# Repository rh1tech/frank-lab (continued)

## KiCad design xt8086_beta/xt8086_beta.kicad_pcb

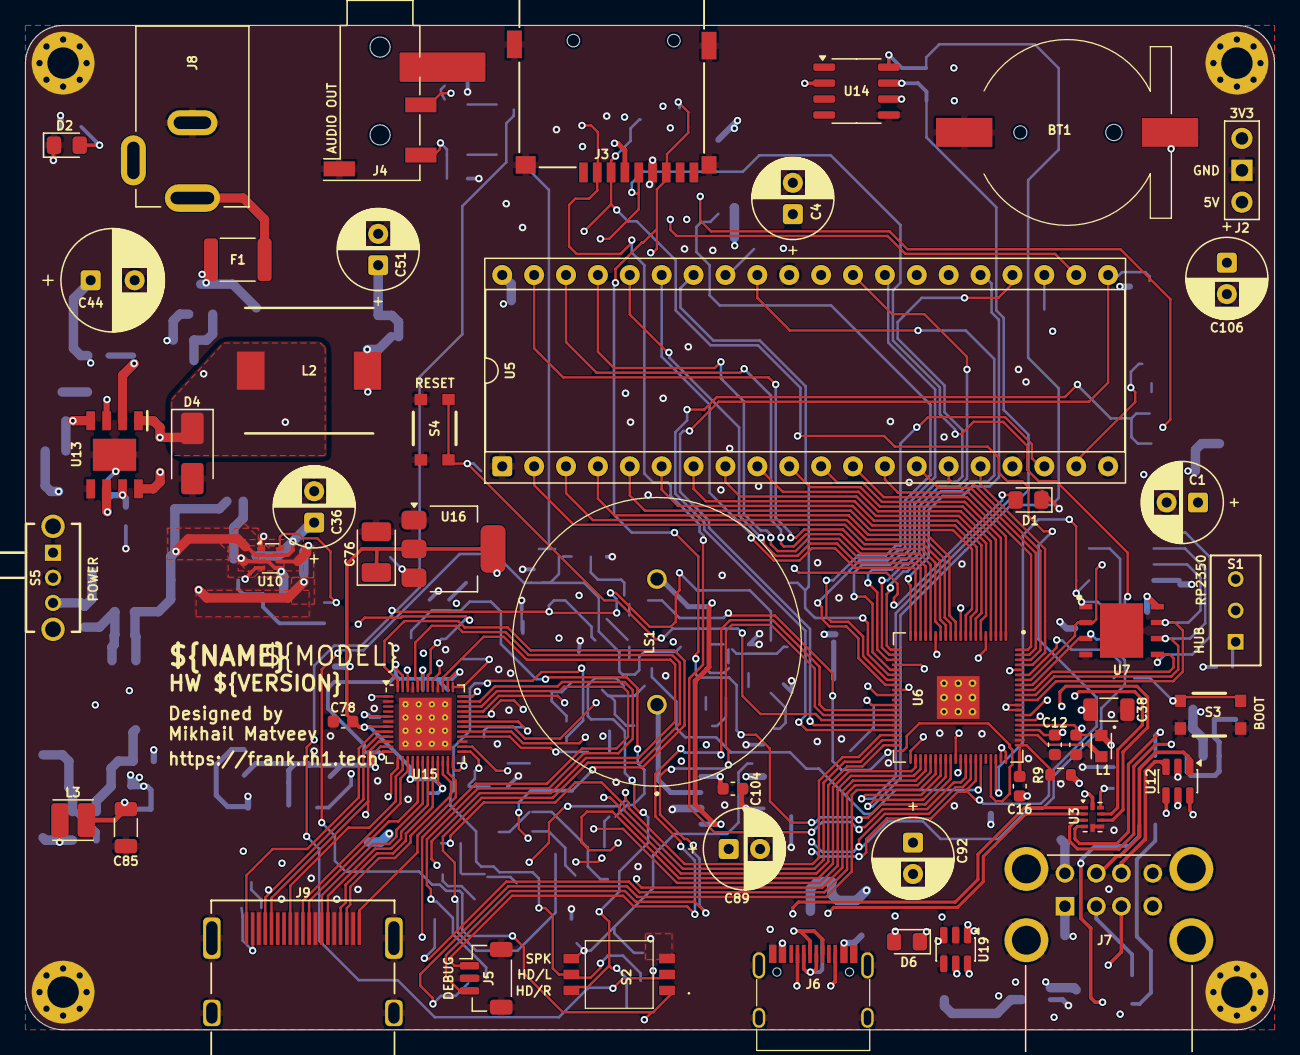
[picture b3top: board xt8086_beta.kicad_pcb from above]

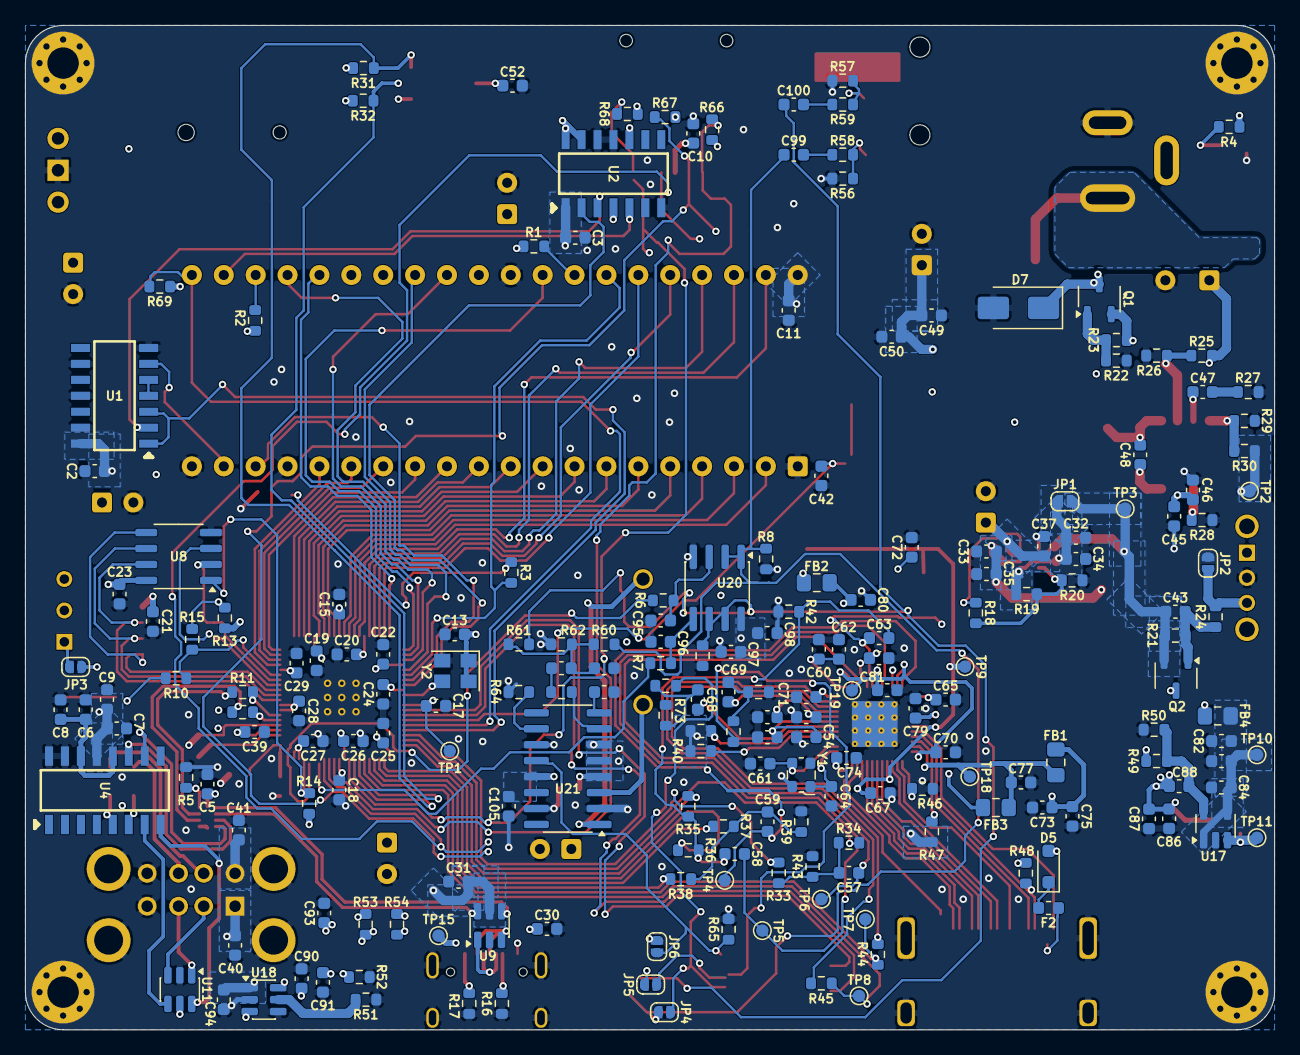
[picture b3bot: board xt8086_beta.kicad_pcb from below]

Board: 4 copper layers, 99.5 x 80.0 mm, 258 parts (203 on the bottom side), 179 nets.

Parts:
BT1: Battery_CR1220
C1, C4, C36, C89, C92, C106: 100u 25V; CP_Radial_D6.3mm_P2.50mm
C2, C3, C5, C8, C9, C10, C11, C13, C15, C18, C19, C20, C21, C22, C23, C24, C25, C26, C27, C28, C29, C30, C31, C32, C33, C37, C39, C46, C48, C49, C52, C57, C58, C59, C65, C66, C67, C70, C71, C74, C75, C84, C87, C93, C94, C97, C104: 100n 50V; C_0603_1608Metric
C6, C43, C68, C69, C78, C79, C102, C103: 1u 50V; C_0603_1608Metric
C7, C12, C14, C16, C17, C54, C56, C62: 4.7u 16V; C_0603_1608Metric
C34, C35, C40, C41, C50, C72, C73, C77, C80, C81, C82, C83, C86, C90, C91, C98, C99, C100, C105: 10u 10V; C_0603_1608Metric
C38, C85: 100u 6.3V; C_1206_3216Metric
C42, C63: 1n 50V; C_0603_1608Metric
C44: 680u 25V; CP_Radial_D8.0mm_P3.50mm
C45: 10u 25V; C_0603_1608Metric
C47: 150p 50V; C_0603_1608Metric
C51: 220u 16V; CP_Radial_D6.3mm_P2.50mm
C53, C55, C60: 220n 25V; C_0603_1608Metric
C61, C64: 15p 50V; C_0603_1608Metric
C76: 22u 16V; CP_EIA-3528-12_Kemet-T
C88: 22p 50V; C_0603_1608Metric
C95, C96: 10n 50V; C_0603_1608Metric
C101: 6.8n 50V; C_0603_1608Metric
D1, D6: Red; LED_0805_2012Metric_Pad1.15x1.40mm_HandSolder
D2: Green; LED_0805_2012Metric_Pad1.15x1.40mm_HandSolder
D4: SS34; D_SMA
D5: 1N5819WS; D_SOD-323
D7: SMAJ15A; D_SMA
F1: 1.5A 24V; Fuse_1812_4532Metric
F2: 0.2A 9V; Fuse_0603_1608Metric
FB1, FB2, FB3: 220Ω@100MHz; L_0805_2012Metric
FB4: 330Ω@100MHz 2A; L_0805_2012Metric
H1, H2, H3, H4: Hole 2.5mm; MountingHole_2.5mm_Pad_Via
J2: PWR; PinHeader_1x03_P2.54mm_Vertical
J3: 693072010801; MicroSD_SMD_Long
J4: PJ-320D; AudioJack_3.5mm_PJ320D_AudioOut
J5: Debug; JST_SH_1x03_P1.00mm_Vertical
J6: USB4215-03-A; USB_C_Receptacle
J7: SS-52100-004; USB_A_Stacked
J8: DC-005-5A-2.0; BarrelJack_DC-005
J9: DC3RX19JA2; HDMI_Female
JP1: Power Debug; SolderJumper-2_P1.0mm_Open_RoundedPad0.7x1.0mm
JP2: Force On; SolderJumper-2_P1.0mm_Open_RoundedPad0.7x1.0mm
JP3: USB Test; SolderJumper-2_P1.0mm_Open_RoundedPad0.7x1.0mm
JP4: Audio L; SolderJumper-2_P1.0mm_Open_RoundedPad0.7x1.0mm
JP5: Audio R; SolderJumper-2_P1.0mm_Open_RoundedPad0.7x1.0mm
JP6: Speaker; SolderJumper-2_P1.0mm_Open_RoundedPad0.7x1.0mm
L1: 3.3µH; L_LQH2MCN100K02L
L2: 22µH; Inductor_CDRH104RNP
L3: 2.2µH; L_Cenker_CKCS3015
LS1: 2308 1W 8Ω; CVS-2308
Q1, Q2: AO3401A; SOT-23-3L_AOS
R1, R2, R3, R4, R6, R7, R10, R46, R54: 1kΩ; R_0603_1608Metric
R5, R13, R14, R24, R63, R64, R65, R66, R67, R68, R69, R73, R75: 10kΩ; R_0603_1608Metric
R8, R55: 2.2kΩ; R_0603_1608Metric
R9: 33Ω; R_0603_1608Metric
R11, R12: 27Ω; R_0603_1608Metric
R15, R72, R74: 0Ω; R_0603_1608Metric
R16, R17: 5.1kΩ; R_0603_1608Metric
R18: 1MΩ; R_0603_1608Metric
R19, R25: 300kΩ; R_0603_1608Metric
R20, R21, R22, R26, R27, R28, R49, R51, R52, R53: 100kΩ; R_0603_1608Metric
R23, R30: 43kΩ; R_0603_1608Metric
R29: 8.2kΩ; R_0603_1608Metric
R31, R32, R40, R41: 4.7kΩ; R_0603_1608Metric
R33, R35, R37: 806Ω; R_0603_1608Metric
R34, R36, R38, R58, R59: 402Ω; R_0603_1608Metric
R39, R42, R43: 75Ω; R_0603_1608Metric
R44, R45: 100Ω; R_0603_1608Metric
R47, R48, R62: 2kΩ; R_0603_1608Metric
R50, R60, R61: 22kΩ; R_0603_1608Metric
R56, R57: 20kΩ; R_0603_1608Metric
S1: SS12D00; Switch_Slide_SS12D00
S2: DS05-127-2-03BK-SMT-TR; SW_DIP_DS05-127-2-03BK-SMT
S3: Boot; Button_SMD_3x4x2mm
S4: Reset; Button_SMD_3x4x2mm
S5: SK12D07VG3NS; Switch_Slide_SK12D07VG3NS
TP1: +1V1; TestPoint_Pad_D1.0mm
TP2: +5V_DC; TestPoint_Pad_D1.0mm
TP3: +5V_SEL; TestPoint_Pad_D1.0mm
TP4: R; TestPoint_Pad_D1.0mm
TP5: G; TestPoint_Pad_D1.0mm
TP6: B; TestPoint_Pad_D1.0mm
TP7: HS; TestPoint_Pad_D1.0mm
TP8: VS; TestPoint_Pad_D1.0mm
TP9: AMS_1V8; TestPoint_Pad_D1.0mm
TP10: +5V_BUCK; TestPoint_Pad_D1.0mm
TP11: LX; TestPoint_Pad_D1.0mm
TP15: VBUS_USB; TestPoint_Pad_D1.0mm
TP18: AMS_3V3; TestPoint_Pad_D1.0mm
TP19: AMS_3V3A; TestPoint_Pad_D1.0mm
U1: 74HCT04; SOIC127P600X175-14N
U2: SN74LS74; SOIC127P600X175-14N
U3: TS3USB221RSER; Texas_R-PUQFN-N10
U4: MW7211A; SOIC127P600X175-16N
U5: 8086_Min_Mode; DIP-40_W15.24mm_Socket
U6: RP2350B; RP2350-QFN-80_10x10_P0.4mm
U7: W25Q128JVPIQ; SON127P600X500X80-9N-D
U8: ESP-PSRAM64H; SO-8
U9, U11, U12: USBLC6-2SC6; SOT-23-6
U10: TPS2116DRL; SOT-583-8
U13: MP1584EN-LF-Z; SOIC-9_P1.27mm
U14: DS3231MZ; SO-8
U15: MS9288A; QFN-48_6x6mm_P0.4mm
U16: AMS1117-1.8; SOT-223-3_TabPin2
U17: SY8089AAAC; SOT-23-5
U18, U19: CH217K; SOT-23-6
U20: LM358; SOIC-8_3.9x4.9mm_P1.27mm
U21: PAM8403D; SOP-16_P1.27mm
Y1: 24.576MHz; Crystal_SMD_2520-4Pin
Y2: 12MHz; Oscillator_SMD_3225_4Pin

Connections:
+1V1: C14.1, C15.1, C17.1, C18.1, L1.1, TP1.1, U6.10 (DVDD), U6.32 (DVDD), U6.51 (DVDD), U6.65 (VREG_FB)
+3V3: C5.2, C10.2, C12.1, C13.1, C19.1, C20.1, C21.1, C22.1, C23.1, C24.1, C25.1, C26.1, C27.1, C28.1, C29.1, C38.1, C39.1, C52.1, C73.1, C75.1, C85.1, C86.1, C87.1, C88.1, FB1.1, J2.3, J3.4 (VDD), JP3.1, L3.2, R4.2, R9.1, R13.2, R14.2, R31.2, R32.2, R40.2, R41.2, R49.1, R66.1, R67.1, R68.1, R69.1, S1.2, U3.10 (VCC), U6.5 (IOVDD), U6.15 (IOVDD), U6.24 (IOVDD), U6.29 (IOVDD), U6.41 (IOVDD), U6.50 (IOVDD), U6.59 (ADC_AVDD), U6.60 (IOVDD), U6.64 (VREG_VIN), U6.68 (USB_OTP_VDD), U6.69 (QSPI_IOVDD), U6.76 (IOVDD), U7.8 (VCC), U8.8 (VCC), U14.2 (VCC), Y2.1 (EN), Y2.4 (Vdd)
+5V_DC: C32.2, C34.2, C49.2, C50.1, C51.1, JP1.1, L2.2, R19.2, R30.1, TP2.1, U10.3 (VIN1), U10.5 (MODE)
+5V_SEL: C31.2, C36.1, C37.1, C43.1, JP1.2, Q2.2 (S), R21.1, TP3.1, U9.5 (VBUS), U10.2 (VOUT), U10.7 (VOUT)
/A16/GP16: U5.38 (A16/S3), U6.16 (GPIO16)
/A17/GP17: U5.37 (A17/S4), U6.17 (GPIO17)
/A18/GP18: U5.36 (A18/S5), U6.18 (GPIO18)
/A19/GP19: U5.35 (A19/S6), U6.19 (GPIO19)
/AD0/GP0: U5.16 (AD0), U6.77 (GPIO0)
/AD1/GP1: U5.15 (AD1), U6.78 (GPIO1)
/AD2/GP2: U5.14 (AD2), U6.79 (GPIO2)
/AD3/GP3: U5.13 (AD3), U6.80 (GPIO3)
/AD4/GP4: U5.12 (AD4), U6.1 (GPIO4)
/AD5/GP5: U5.11 (AD5), U6.2 (GPIO5)
/AD6/GP6: U5.10 (AD6), U6.3 (GPIO6)
/AD7/GP7: U5.9 (AD7), U6.4 (GPIO7)
/AD8/GP8: U5.8 (AD8), U6.6 (GPIO8)
/AD9/GP9: U5.7 (AD9), U6.7 (GPIO9)
/AD10/GP10: U5.6 (AD10), U6.8 (GPIO10)
/AD11/GP11: U5.5 (AD11), U6.9 (GPIO11)
/AD12/GP12: U5.4 (AD12), U6.11 (GPIO12)
/AD13/GP13: U5.3 (AD13), U6.12 (GPIO13)
/AD14/GP14: U5.2 (AD14), U6.13 (GPIO14)
/AD15/GP15: U5.39 (AD15), U6.14 (GPIO15)
/ALE/GP20: U5.25 (ALE), U6.20 (GPIO20)
/BHE/GP25: R3.2, U5.34 (~BHE/S7), U6.26 (GPIO25)
/CLK_5V: U1.6 (3Y), U5.19 (CLK)
/CLK/GP29: U1.1 (1A), U1.3 (2A), U6.37 (GPIO29)
/GP27: U2.2 (D1), U6.28 (GPIO27)
/HDMI_L: JP4.2, R72.1, S2.2
/HDMI_R: JP5.2, R74.1, S2.4
/INTA/GP23: U5.24 (~INTA), U6.23 (GPIO23)
/INTR/GP26: U5.18 (INTR), U6.27 (GPIO26)
/MIO/GP24: U5.28 (M/~IO), U6.25 (GPIO24)
/MN/MX: R1.2, U5.33 (MN/~MX)
/Micro SD/CDDAT3: J3.2 (DAT3/CD), R66.2, U6.52 (GPIO41_ADC1)
/Micro SD/CLK: J3.5 (CLK), U6.53 (GPIO42_ADC2)
/Micro SD/CMD: J3.3 (CMD), R67.2, U6.54 (GPIO43_ADC3)
/Micro SD/DAT0: J3.7 (DAT0), R68.2, U6.49 (GPIO40_ADC0)
/PWM_L: R6.1, U6.57 (GPIO46_ADC6)
/PWM_R: R7.1, U6.55 (GPIO44_ADC4)
/RD/GP21: U5.32 (~RD), U6.21 (GPIO21)
/READY: U2.5 (Q1), U5.22 (READY)
/RESET/GP28: R69.2, U5.21 (RESET), U6.36 (GPIO28)
/RP2350B/DM: R12.1, U3.7 (D-)
/RP2350B/DP: R11.1, U3.8 (D+)
/RP2350B/GP30: R33.1, U6.38 (GPIO30)
/RP2350B/GP31: R34.1, U6.39 (GPIO31)
/RP2350B/GP32: R35.1, U6.40 (GPIO32)
/RP2350B/GP33: R36.1, U6.42 (GPIO33)
/RP2350B/GP34: R37.1, U6.43 (GPIO34)
/RP2350B/GP35: R38.1, U6.44 (GPIO35)
/RP2350B/GP36: R44.1, TP7.1, U6.45 (GPIO36)
/RP2350B/GP37: R45.1, TP8.1, U6.46 (GPIO37)
/RP2350B/GP38: R32.1, U6.47 (GPIO38), U14.7 (SDA)
/RP2350B/GP39: R31.1, U6.48 (GPIO39), U14.8 (SCL)
/RP2350B/GP47: R14.1, U6.58 (GPIO47_ADC7), U8.1 (~CE)
/RP2350B/QSPI_SCLK: U6.71 (QSPI_SCLK), U7.6 (CLK), U8.6 (SCLK)
/RP2350B/QSPI_SD0: U6.72 (QSPI_SD0), U7.5 (DI_(IO0)), U8.5 (SI/SIO)
/RP2350B/QSPI_SD1: U6.74 (QSPI_SD1), U7.2 (DO_(IO1)), U8.2 (SO/SIO)
/RP2350B/QSPI_SD2: U6.73 (QSPI_SD2), U7.3 (~WP_(IO2)), U8.3 (SIO2)
/RP2350B/QSPI_SD3: U6.70 (QSPI_SD3), U7.7 (~HOLD_OR_/RESET_(IO3)), U8.7 (SIO3)
/RP2350B/QSPI_SS: R10.1, R15.1, U6.75 (QSPI_SS)
/RP2350B/Reset/RESET: C42.2, S4.2, S4.4, U6.35 (RUN)
/RP2350B/SWCLK: J5.3, U6.33 (SWCLK)
/RP2350B/SWD: J5.1, U6.34 (SWD)
/RP2350B/VREG_AVDD: C16.1, R9.2, U6.61 (VREG_AVDD)
/RP2350B/VREG_LX: L1.2, U6.63 (VREG_LX)
/RP2350B/XIN: U6.30 (XIN), Y2.3 (OUT)
/RP2350B/~USB_BOOT: R10.2, S3.2, S3.4
/Sound/AUDIO_L: C99.2, JP4.1, R8.1, R60.1, S2.1, U20.1, U20.2
/Sound/AUDIO_R: C100.2, JP5.1, R55.1, R61.1, S2.3, U20.6, U20.7
/Sound/SPK_EN: JP6.2, R65.1, S2.6, U21.12
/Sound/Speaker/SPK_N: LS1.1, U21.3
/Sound/Speaker/SPK_P: LS1.2, U21.1
/TEST: R2.2, U5.23 (~TEST)
/USB, Power/3V3 Buck/+5V_BUCK: C82.1, C83.1, C84.1, FB4.2, TP10.1, U17.1 (EN), U17.4 (IN)
/USB, Power/3V3 Buck/FB: C88.2, R49.2, R50.1, U17.5 (FB)
/USB, Power/Power/VIN: C44.1, C45.1, C46.1, Q1.2 (S), R23.2, R25.2, U13.7 (VIN)
/USB, Power/ST: R18.1, U10.8 (ST)
/USB, Power/SW: JP3.2, R5.1, S1.1, U3.9 (S)
/USB, Power/UA1M: U4.7 (DM3), U11.4 (I/O2)
/USB, Power/UA1P: U4.8 (DP3), U11.6 (I/O1)
/USB, Power/UA2M: U4.5 (DM2), U12.6 (I/O1)
/USB, Power/UA2P: U4.6 (DP2), U12.4 (I/O2)
/USB, Power/UAM: U3.4 (2D-), U4.10 (DMU)
/USB, Power/UAP: U3.3 (2D+), U4.11 (DPU)
/USB, Power/UCM: U3.2 (1D-), U9.6 (I/O1)
/USB, Power/UCP: U3.1 (1D+), U9.4 (I/O2)
/USB, Power/USB Hub/VD33: C6.1, C8.1, U4.12 (VD33), U4.14 (VD3)
/USB, Power/USB-A Port Power/USB_OC: D6.1 (K), R53.2, U18.3 (FLAG#), U19.3 (FLAG#)
/USB, Power/VBUS_P1: C40.1, C94.1, J7.1 (VBUS1), U18.1 (VOUT)
/USB, Power/VBUS_P2: C41.1, C93.1, J7.5 (VBUS2), U19.1 (VOUT)
/USB, Power/VBUS_USB: C30.1, C33.2, C35.2, J6.2 (VBUS), J6.11 (VBUS), TP15.1, U10.6 (VIN2)
/Video/ALIN: C68.1, U15.30 (ALIN)
/Video/AMS_1V8: C67.1, C76.1, C78.1, FB2.1, TP9.1, U15.7 (AVDD18), U15.16 (AVDD18), U15.21 (AVDD18), U16.2 (VO)
/Video/AMS_1V8A: C65.1, C66.1, C80.1, FB2.2, U15.1 (AVDD18_ADC), U15.41 (AVDD18_ADC), U15.46 (AVDD18_ADC)
/Video/AMS_3V3: C71.1, C72.1, C74.1, C77.1, C79.1, FB1.2, FB3.1, TP18.1, U15.5 (DVDD33), U15.11 (DVDD33), U15.24 (DVDD33), U15.36 (DVDD33), U16.3 (VI)
/Video/AMS_3V3A: C70.1, C81.1, FB3.2, TP19.1, U15.12 (AVDD33), U15.38 (AVDD33), U15.43 (AVDD33), U15.47 (AVDD33)
/Video/ARIN: C69.1, U15.33 (ARIN)
/Video/B: C57.1, TP6.1, U15.39 (B/Pb)
/Video/DCCSCL: J9.15 (SCL), R47.1, U15.10 (DCCSCL)
/Video/DDCSDA: J9.16 (SDA), R48.1, U15.9 (DDCSDA)
/Video/G: C58.1, TP5.1, U15.44 (G/Y)
/Video/HPDT: J9.19 (HOT_PLUG_DET), U15.8 (HotPlugDetect)
/Video/R: C59.1, TP4.1, U15.48 (R/Pr)
/Video/SCL: R40.1, U15.28 (SCL)
/Video/SDA: R41.1, U15.29 (SDA)
/Video/SOG_G: C58.2, C63.2, R35.2, R36.2, R42.1
/Video/TMDS_CLK+: J9.10 (CLKP), U15.15 (TMDS_CLK+)
/Video/TMDS_CLK-: J9.12 (CLKN), U15.14 (TMDS_CLK-)
/Video/TMDS_D0+: J9.7 (D0P), U15.18 (TMDS-D0+)
/Video/TMDS_D0-: J9.9 (D0N), U15.17 (TMDS_D0-)
/Video/TMDS_D1+: J9.4 (D1P), U15.20 (TMDS_D1+)
/Video/TMDS_D1-: J9.6 (D1N), U15.19 (TMDS_D1-)
/Video/TMDS_D2+: J9.1 (D2P), U15.23 (TMDS_D2+)
/Video/TMDS_D2-: J9.3 (D2N), U15.22 (TMDS_D2-)
/WR/GP22: U5.29 (~WR), U6.22 (GPIO22)
GND: BT1.2 (-), C1.2, C2.2, C3.2, C4.2, C5.1, C6.2, C7.2, C8.2, C9.2, C10.1, C11.2, C12.2, C13.2, C14.2, C15.2, C16.2, C17.2, C18.2, C19.2, C20.2, C21.2, C22.2, C23.2, C24.2, C25.2, C26.2, C27.2, C28.2, C29.2, C30.2, C31.1, C32.1, C33.1, C34.1, C35.1, C36.2, C37.2, C38.2, C39.2, C40.2, C41.2, C42.1, C44.2, C45.2, C46.2, C49.1, C50.2, C51.2, C52.2, C53.2, C54.2, C55.2, C56.2, C60.2, C61.2, C62.2, C64.2, C65.2, C66.2, C67.2, C70.2, C71.2, C72.2, C73.2, C74.2, C75.2, C76.2, C77.2, C78.2, C79.2, C80.2, C81.2, C82.2, C83.2, C84.2, C85.2, C86.2, C87.2, C89.2, C90.2, C91.2, C92.2, C93.2, C94.2, C95.2, C96.2, C97.2, C98.2, C101.2, C103.2, C104.2, C105.2, C106.2, D1.1 (K), D2.1 (K), D4.2 (A), D7.2 (A), H1.1, H2.1, H3.1, H4.1, J2.2, J3.6 (VSS), J3.SH (SHIELD), J4.S, J5.2, J6.1 (GND), J6.12 (GND), J6.13 (SHIELD), J7.4 (GND1), J7.8 (GND2), J7.SH (Shield), J8.2, J9.2 (G_D2), J9.5 (G_D1), J9.8 (G_D0), J9.11 (G_CLK), J9.17 (G_DDC/CEC), J9.20 (SHIELD1), J9.21 (SHIELD2), J9.22 (SHIELD3), J9.23 (SHIELD4), JP2.1, R5.2, R8.2, R16.1, R17.1, R20.1, R22.2, R26.2, R27.2, R28.2, R29.1, R39.2, R42.2, R43.2, R46.1, R50.2, R51.2, R52.2, R55.2, R56.2, R57.2, R62.2, R64.2, R65.2, R73.2, R75.2, S3.1, S3.3, S4.1, S4.3, S5.2, U1.7 (GND), U1.9 (4A), U1.11 (5A), U1.13 (6A), U2.7 (GND), U2.11 (CLK2), U2.12 (D2), U3.5 (GND), U3.6 (~OE), U4.15 (GND), U4.16 (GND), U5.1 (GND), U5.17 (NMI), U5.20 (GND), U5.31 (HOLD), U6.62 (VREG_PGND), U6.81 (GND), U7.4 (GND_1), U7.9 (GND_2), U8.4 (VSS), U9.2 (GND), U10.1 (GND), U11.2 (GND), U12.2 (GND), U13.5 (GND), U13.9 (EP), U14.5 (GND), U15.2 (GND), U15.6 (GND), U15.27 (GND), U15.40 (GND), U15.45 (GND), U15.49 (EP), U16.1 (GND), U17.2 (GND), U18.2 (GND), U18.4 (EN#), U19.2 (GND), U19.4 (EN#), U20.4, U21.2, U21.11, U21.15, Y1.2 (GND), Y1.4 (GND), Y2.2 (GND)
unnamed: BT1.1 (+), U14.6 (VBAT)
unnamed: C47.2, R27.1
unnamed: C57.2, R33.2, R34.2, R43.1
unnamed: C59.2, R37.2, R38.2, R39.1
unnamed: C68.2, R72.2, R73.1
unnamed: C69.2, R74.2, R75.1
unnamed: C99.1, R58.2
unnamed: C100.1, R59.2
unnamed: C101.1, C102.1, R60.2, R61.2, R62.1
unnamed: C102.2, R63.1
unnamed: D1.2 (A), R3.1
unnamed: D2.2 (A), R4.1
unnamed: C48.2, D4.1 (K), L2.1, U13.1 (SW)
unnamed: D5.1 (K), F2.2
unnamed: D6.2 (A), R54.2
unnamed: D7.1 (K), F1.2, Q1.3 (D)
unnamed: F1.1, J8.1
unnamed: J4.R, R57.1, R59.1
unnamed: J4.T, R56.1, R58.1
unnamed: J6.4 (CC1), R16.2
unnamed: J6.10 (CC2), R17.2
unnamed: J6.5 (DN2), J6.7 (DN1), U9.1 (I/O1)
unnamed: J6.6 (DP1), J6.8 (DP2), U9.3 (I/O2)
unnamed: J7.3 (D1+), U11.1 (I/O1)
unnamed: J7.2 (D1-), U11.3 (I/O2)
unnamed: J7.7 (D2+), U12.3 (I/O2)
unnamed: J7.6 (D2-), U12.1 (I/O1)
unnamed: F2.1, J9.18 (+5V)
unnamed: JP2.2, R24.2, S5.3
unnamed: Q1.1 (G), R22.1, R23.1
unnamed: C43.2, Q2.1 (G), R21.2, R24.1
unnamed: U1.2 (1Y), U2.3 (CLK1)
unnamed: U1.4 (2Y), U1.5 (3A)
unnamed: R12.2, U6.66 (USB_DM)
unnamed: R11.2, U6.67 (USB_DP)
unnamed: R13.1, R15.2, U7.1 (~CS)
unnamed: R18.2, R19.1, R20.2, U10.4 (PR1)
unnamed: C48.1, U13.8 (BST)
unnamed: C47.1, U13.3 (COMP)
unnamed: R25.1, R26.1, U13.2 (EN)
unnamed: R29.2, R30.2, U13.4 (FB)
unnamed: R28.1, U13.6 (FREQ)
unnamed: R44.2, U15.34 (HSIN)
unnamed: C60.1, C62.1, U15.37 (REFP)
unnamed: C53.1, C54.1, U15.31 (REFQ0)
unnamed: C55.1, C56.1, U15.32 (REFQ1)
unnamed: C63.1, U15.42 (SOG/Y)
unnamed: R46.2, U15.13 (SWREF1k)
unnamed: R45.2, U15.35 (VSIN)
unnamed: C64.1, U15.25 (XTI), Y1.1 (OSC)
unnamed: C61.1, U15.26 (XTO), Y1.3 (OSC)
unnamed: L3.1, TP11.1, U17.3 (LX)
unnamed: R51.1, U18.5 (ISET)
unnamed: R52.1, U19.5 (ISET)
unnamed: C95.1, R6.2, U20.3
unnamed: C96.1, R7.2, U20.5
unnamed: R63.2, U21.7
unnamed: R64.1, U21.10
unnamed: C103.1, U21.8
VBUS: C1.1, C2.1, C3.1, C4.1, C7.1, C9.1, C11.1, C89.1, C90.1, C91.1, C92.1, C97.1, C98.1, C104.1, C105.1, C106.1, D5.2 (A), FB4.1, J2.1, JP6.1, Q2.3 (D), R1.1, R2.1, R47.2, R48.2, R53.1, R54.1, S2.5, U1.14 (VCC), U2.1 (CLR1), U2.4 (PR1), U2.10 (PR2), U2.13 (CLR2), U2.14 (VCC), U4.13 (VDD5), U5.40 (VCC), U11.5 (VBUS), U12.5 (VBUS), U18.6 (VIN), U19.6 (VIN), U20.8, U21.4, U21.5, U21.6, U21.13

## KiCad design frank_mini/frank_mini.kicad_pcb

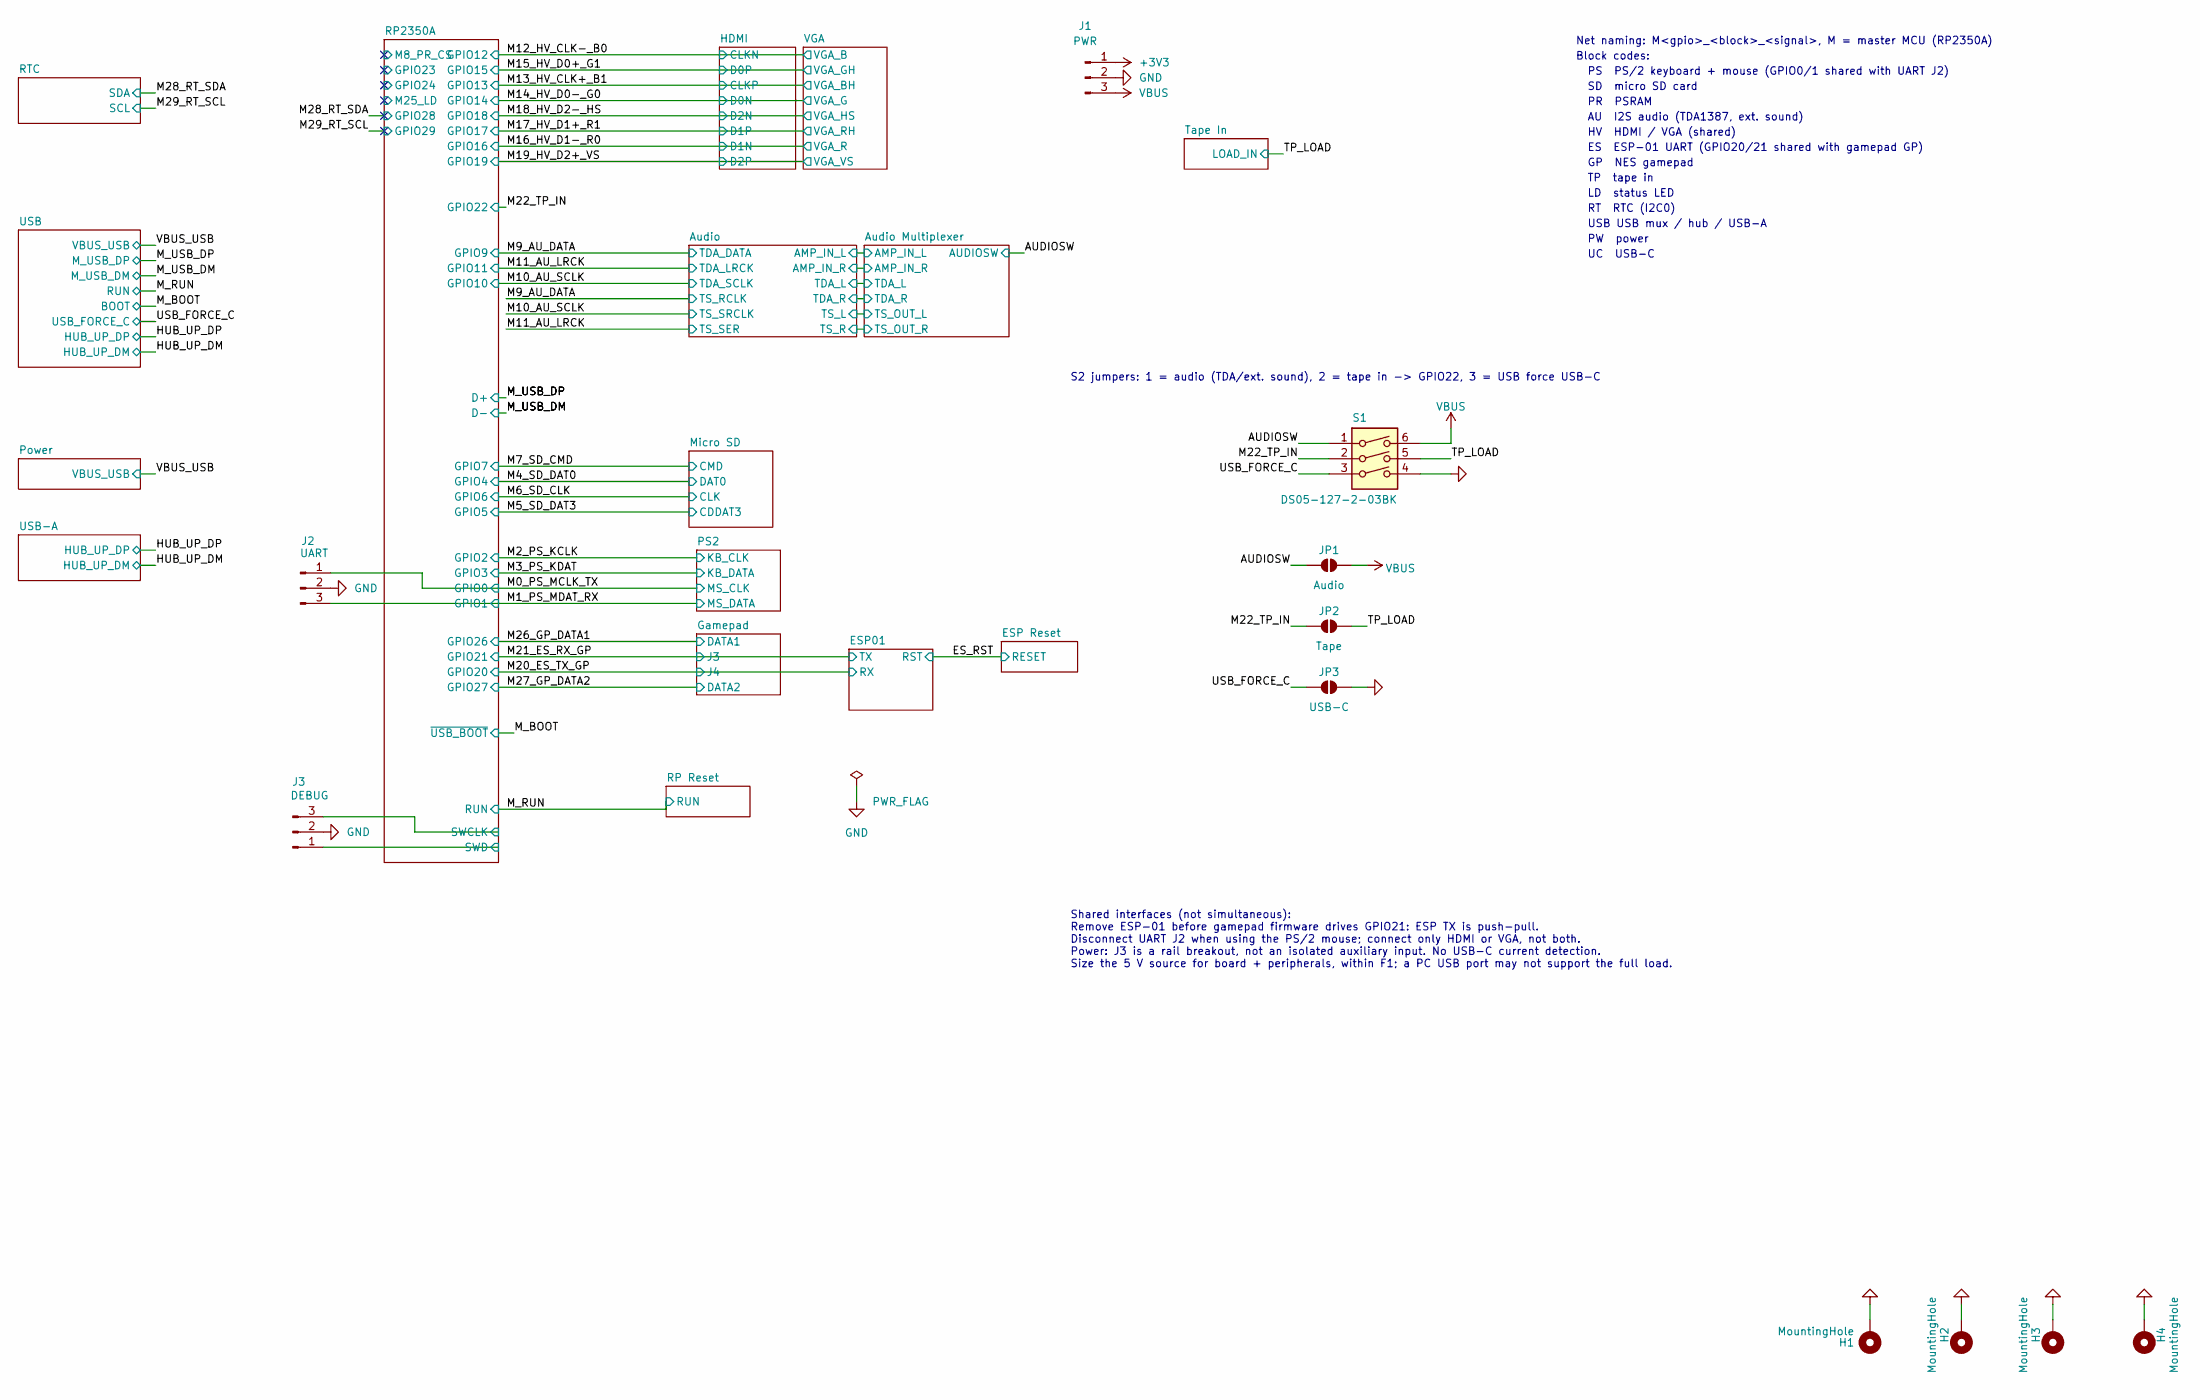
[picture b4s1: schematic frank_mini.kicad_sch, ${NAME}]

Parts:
H1, H2, H3, H4: MountingHole; MountingHole_2.5mm_Pad_Via
J1: PWR; PinHeader_1x03_P2.54mm
J2: UART; JST_SH_BM03B-SRSS-TB_1x03-1MP_P1.00mm_Vertical
J3: DEBUG; JST_SH_BM03B-SRSS-TB_1x03-1MP_P1.00mm_Vertical
JP1: Audio; SolderJumper-2_P1.3mm_Open_RoundedPad1.0x1.5mm
JP2: Tape; SolderJumper-2_P1.3mm_Open_RoundedPad1.0x1.5mm
JP3: USB-C; SolderJumper-2_P1.3mm_Open_RoundedPad1.0x1.5mm
S1: DS05-127-2-03BK; SW_DS05-127-2-03BK-SMT-TR

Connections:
+3V3: J1.1; also elsewhere on the board
/AUDIOSW: JP1.1 (A), S1.1; also elsewhere on the board
/M0_PS_MCLK_TX: J2.1; also elsewhere on the board
/M1_PS_MDAT_RX: J2.3; also elsewhere on the board
/M22_TP_IN: JP2.1 (A), S1.2; also elsewhere on the board
/RP2350A/SWCLK: J3.3; also elsewhere on the board
/RP2350A/SWD: J3.1; also elsewhere on the board
/TP_LOAD: JP2.2 (B), S1.5; also elsewhere on the board
/USB_FORCE_C: JP3.1 (A), S1.3; also elsewhere on the board
GND: H1.1 (1_1), H2.1 (1_1), H3.1 (1_1), H4.1 (1_1), J1.2, J2.2, J3.2, JP3.2 (B), S1.4; also elsewhere on the board
VBUS: J1.3, JP1.2 (B), S1.6; also elsewhere on the board

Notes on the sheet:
UC USB-C
AU I2S audio (TDA1387, ext. sound)
S2 jumpers: 1 = audio (TDA/ext. sound), 2 = tape in -> GPIO22, 3 = USB force USB-C
TP tape in
PS PS/2 keyboard + mouse (GPIO0/1 shared with UART J2)
SD micro SD card
USB USB mux / hub / USB-A
PW power
GP NES gamepad
RT RTC (I2C0)
Block codes:
LD status LED
PR PSRAM
Net naming: M<gpio>_<block>_<signal>, M = master MCU (RP2350A)
HV HDMI / VGA (shared)
ES ESP-01 UART (GPIO20/21 shared with gamepad GP)
Shared interfaces (not simultaneous): Remove ESP-01 before gamepad firmware drives GPIO21: ESP TX is push-pull. Disconnect UART J2 when using the PS/2 mouse; connect only HDMI or VGA, not both. Power: J3 is a rail breakout, not an isolated auxiliary input. No USB-C current detection. Size the 5 V s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

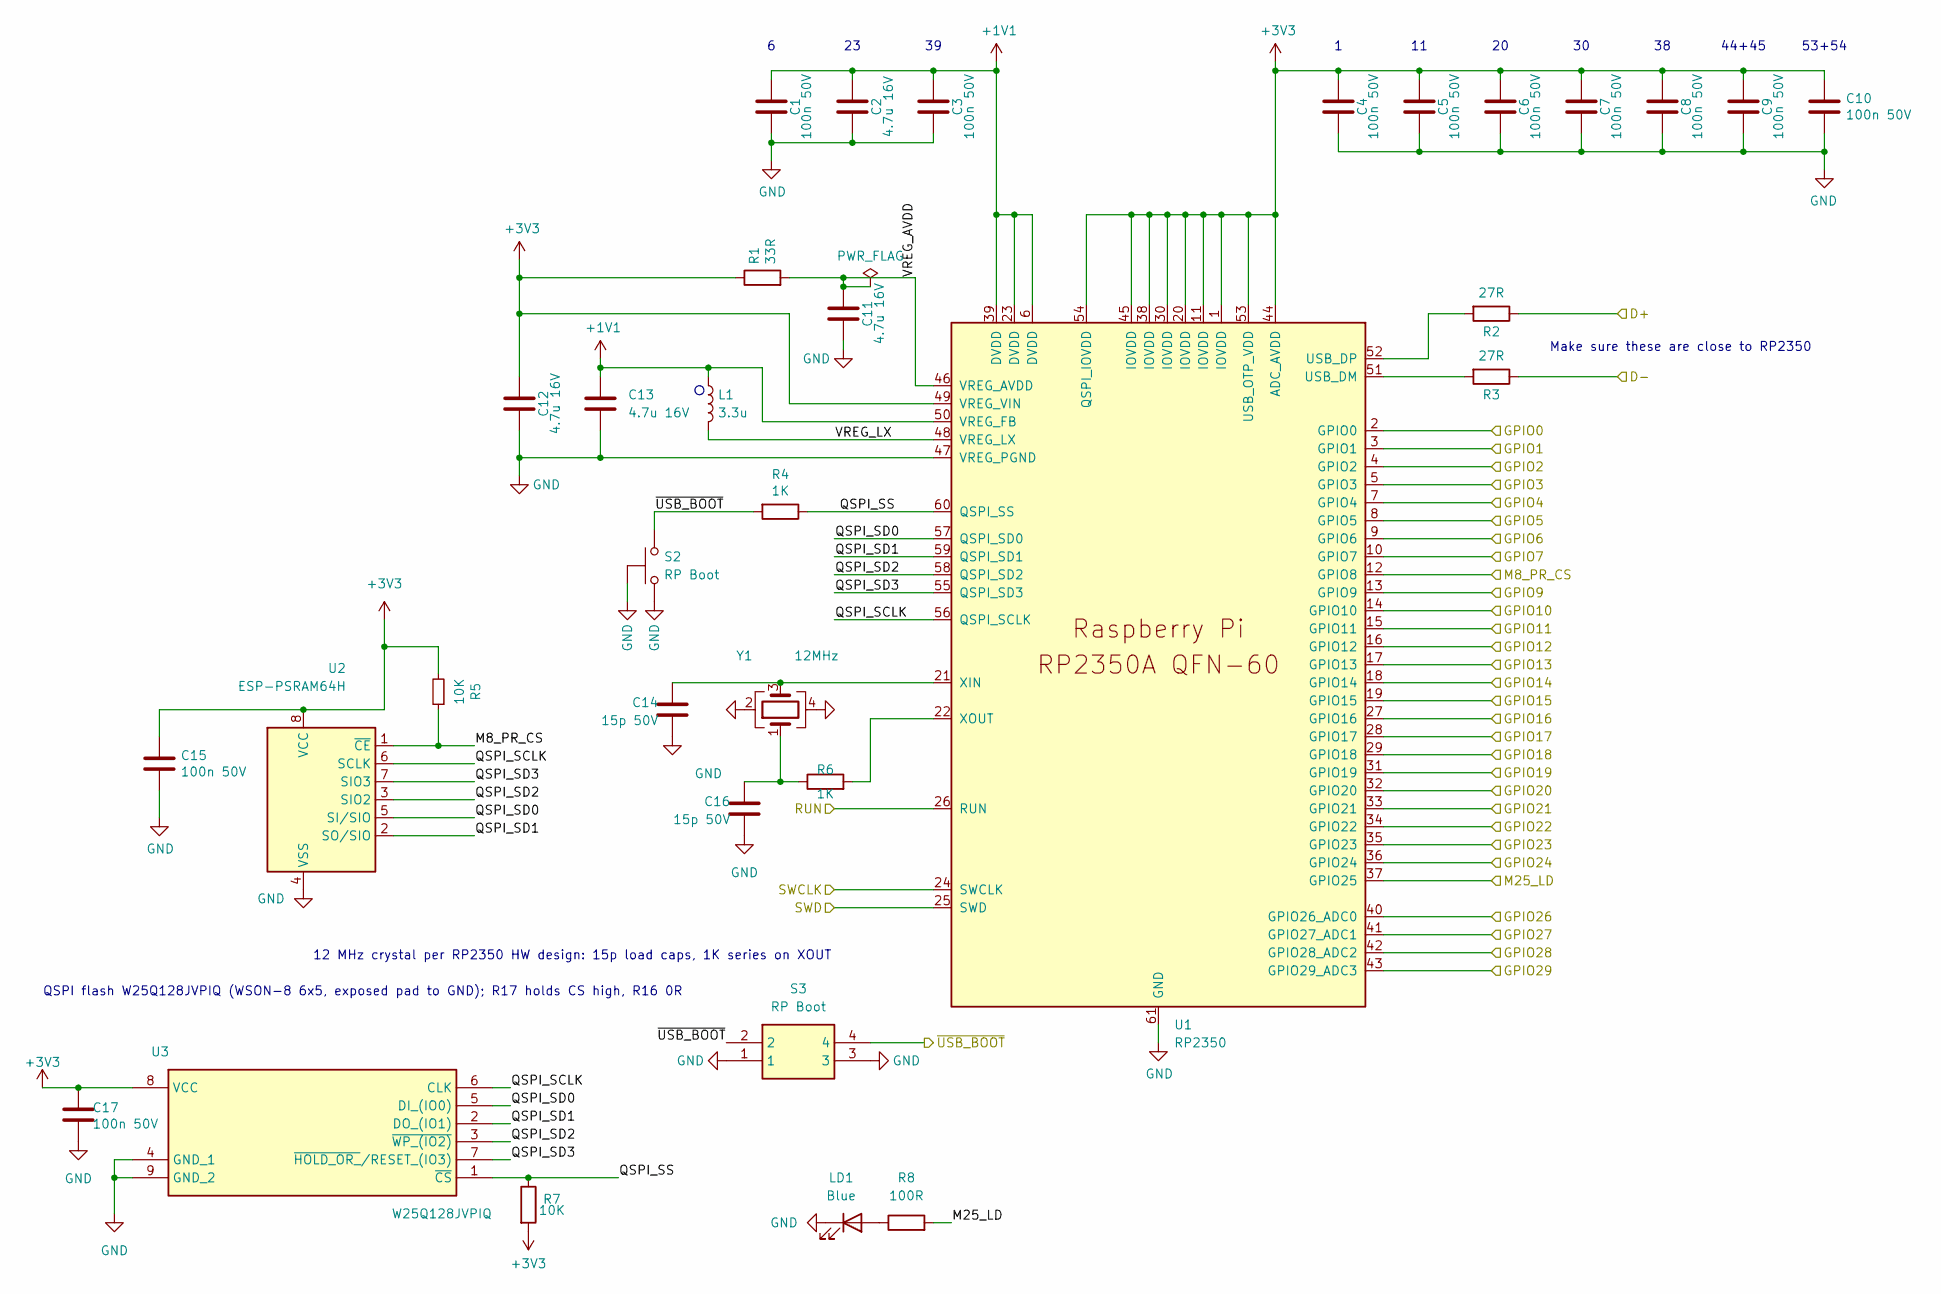
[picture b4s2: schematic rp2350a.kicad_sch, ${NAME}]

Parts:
C1, C3, C4, C5, C6, C7, C8, C9, C10, C15, C17: 100n 50V; C_0603_1608Metric
C2, C11, C12, C13: 4.7u 16V; C_0603_1608Metric
C14, C16: 15p 50V; C_0603_1608Metric
L1: 3.3u; L_pol_2016
LD1: Blue; LED_0603_1608Metric
R1: 33R; R_0603_1608Metric
R2, R3: 27R; R_0603_1608Metric
R4, R6: 1K; R_0603_1608Metric
R5, R7: 10K; R_0603_1608Metric
R8: 100R; R_0603_1608Metric
S2: RP Boot; TS-1234VW
S3: RP Boot; KMR_2; Mouser Part Number 611-KMR221G-LFS
U1: RP2350; QFN-60_RP2350A
U2: ESP-PSRAM64H; SO-8
U3: W25Q128JVPIQ; WSON-8-1EP_6x5mm_P1.27mm_EP3.45x4.35mm
Y1: 12MHz; Crystal_SMD_3225-4Pin_3.2x2.5mm

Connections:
+1V1: C1.1, C2.1, C3.1, C13.1, L1.1, U1.6 (DVDD), U1.23 (DVDD), U1.39 (DVDD), U1.50 (VREG_FB); also elsewhere on the board
+3V3: C4.1, C5.1, C6.1, C7.1, C8.1, C9.1, C10.1, C12.1, C15.1, C17.1, R1.1, R5.2, R7.2, U1.1 (IOVDD), U1.11 (IOVDD), U1.20 (IOVDD), U1.30 (IOVDD), U1.38 (IOVDD), U1.44 (ADC_AVDD), U1.45 (IOVDD), U1.49 (VREG_VIN), U1.53 (USB_OTP_VDD), U1.54 (QSPI_IOVDD), U2.8 (VCC), U3.8 (VCC); also elsewhere on the board
/M0_PS_MCLK_TX: U1.2 (GPIO0); also elsewhere on the board
/M1_PS_MDAT_RX: U1.3 (GPIO1); also elsewhere on the board
/M2_PS_KCLK: U1.4 (GPIO2); also elsewhere on the board
/M3_PS_KDAT: U1.5 (GPIO3); also elsewhere on the board
/M4_SD_DAT0: U1.7 (GPIO4); also elsewhere on the board
/M5_SD_DAT3: U1.8 (GPIO5); also elsewhere on the board
/M6_SD_CLK: U1.9 (GPIO6); also elsewhere on the board
/M7_SD_CMD: U1.10 (GPIO7); also elsewhere on the board
/M9_AU_DATA: U1.13 (GPIO9); also elsewhere on the board
/M10_AU_SCLK: U1.14 (GPIO10); also elsewhere on the board
/M11_AU_LRCK: U1.15 (GPIO11); also elsewhere on the board
/M12_HV_CLK-_B0: U1.16 (GPIO12); also elsewhere on the board
/M13_HV_CLK+_B1: U1.17 (GPIO13); also elsewhere on the board
/M14_HV_D0-_G0: U1.18 (GPIO14); also elsewhere on the board
/M15_HV_D0+_G1: U1.19 (GPIO15); also elsewhere on the board
/M16_HV_D1-_R0: U1.27 (GPIO16); also elsewhere on the board
/M17_HV_D1+_R1: U1.28 (GPIO17); also elsewhere on the board
/M18_HV_D2-_HS: U1.29 (GPIO18); also elsewhere on the board
/M19_HV_D2+_VS: U1.31 (GPIO19); also elsewhere on the board
/M20_ES_TX_GP: U1.32 (GPIO20); also elsewhere on the board
/M21_ES_RX_GP: U1.33 (GPIO21); also elsewhere on the board
/M22_TP_IN: U1.34 (GPIO22); also elsewhere on the board
/M26_GP_DATA1: U1.40 (GPIO26_ADC0); also elsewhere on the board
/M27_GP_DATA2: U1.41 (GPIO27_ADC1); also elsewhere on the board
/M28_RT_SDA: U1.42 (GPIO28_ADC2); also elsewhere on the board
/M29_RT_SCL: U1.43 (GPIO29_ADC3); also elsewhere on the board
/M_BOOT: R4.2, S2.2, S3.2, S3.4; also elsewhere on the board
/M_RUN: U1.26 (RUN); also elsewhere on the board
/M_USB_DM: R3.1; also elsewhere on the board
/M_USB_DP: R2.1; also elsewhere on the board
/RP2350A/GPIO23: U1.35 (GPIO23)
/RP2350A/GPIO24: U1.36 (GPIO24)
/RP2350A/M8_PR_CS: R5.1, U1.12 (GPIO8), U2.1 (~CE)
/RP2350A/M25_LD: R8.2, U1.37 (GPIO25)
/RP2350A/QSPI_SCLK: U1.56 (QSPI_SCLK), U2.6 (SCLK), U3.6 (CLK)
/RP2350A/QSPI_SD0: U1.57 (QSPI_SD0), U2.5 (SI/SIO), U3.5 (DI_(IO0))
/RP2350A/QSPI_SD1: U1.59 (QSPI_SD1), U2.2 (SO/SIO), U3.2 (DO_(IO1))
/RP2350A/QSPI_SD2: U1.58 (QSPI_SD2), U2.3 (SIO2), U3.3 (~WP_(IO2))
/RP2350A/QSPI_SD3: U1.55 (QSPI_SD3), U2.7 (SIO3), U3.7 (~HOLD_OR_/RESET_(IO3))
/RP2350A/QSPI_SS: R4.1, R7.1, U1.60 (QSPI_SS), U3.1 (~CS)
/RP2350A/SWCLK: U1.24 (SWCLK); also elsewhere on the board
/RP2350A/SWD: U1.25 (SWD); also elsewhere on the board
/RP2350A/VREG_AVDD: C11.1, R1.2, U1.46 (VREG_AVDD)
/RP2350A/VREG_LX: L1.2, U1.48 (VREG_LX)
GND: C1.2, C2.2, C3.2, C4.2, C5.2, C6.2, C7.2, C8.2, C9.2, C10.2, C11.2, C12.2, C13.2, C14.2, C15.2, C16.2, C17.2, LD1.1 (K), S2.1, S2.3 (GND), S3.1, S3.3, U1.47 (VREG_PGND), U1.61 (GND), U2.4 (VSS), U3.4 (GND_1), U3.9 (GND_2), Y1.2, Y1.4; also elsewhere on the board
unnamed: C16.1, R6.1, Y1.1
unnamed: LD1.2 (A), R8.1
unnamed: R3.2, U1.51 (USB_DM)
unnamed: R2.2, U1.52 (USB_DP)
unnamed: C14.1, U1.21 (XIN), Y1.3
unnamed: R6.2, U1.22 (XOUT)

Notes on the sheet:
12 MHz crystal per RP2350 HW design: 15p load caps, 1K series on XOUT
53+54
44+45
Make sure these are close to RP2350
QSPI flash W25Q128JVPIQ (WSON-8 6x5, exposed pad to GND); R17 holds CS high, R16 0R

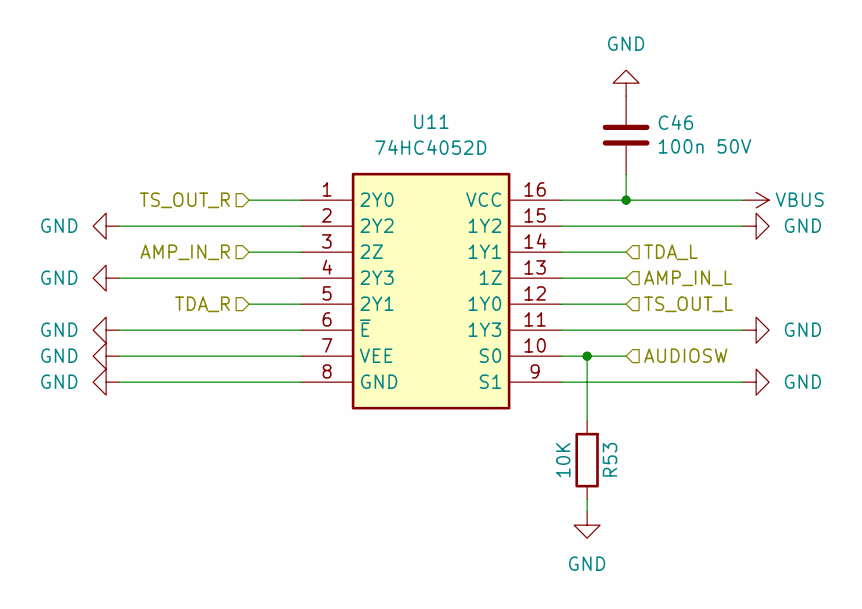
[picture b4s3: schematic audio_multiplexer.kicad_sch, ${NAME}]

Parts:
C46: 100n 50V; C_0603_1608Metric
R53: 10K; R_0603_1608Metric
U11: 74HC4052D; SOP-16_P1.27mm; Mouser Part Number 771-74HC4052D-T

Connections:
/AUDIOSW: R53.2, U11.10 (S0); also elsewhere on the board
/Audio Multiplexer/AMP_IN_L: U11.13 (1Z); also elsewhere on the board
/Audio Multiplexer/AMP_IN_R: U11.3 (2Z); also elsewhere on the board
/Audio Multiplexer/TDA_L: U11.14 (1Y1); also elsewhere on the board
/Audio Multiplexer/TDA_R: U11.5 (2Y1); also elsewhere on the board
/Audio Multiplexer/TS_OUT_L: U11.12 (1Y0); also elsewhere on the board
/Audio Multiplexer/TS_OUT_R: U11.1 (2Y0); also elsewhere on the board
GND: C46.1, R53.1, U11.2 (2Y2), U11.4 (2Y3), U11.6 (~E), U11.7 (VEE), U11.8 (GND), U11.9 (S1), U11.11 (1Y3), U11.15 (1Y2); also elsewhere on the board
VBUS: C46.2, U11.16 (VCC); also elsewhere on the board

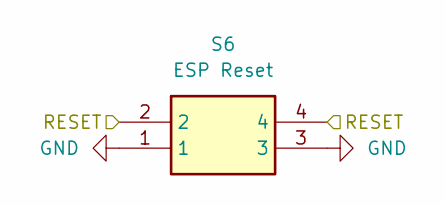
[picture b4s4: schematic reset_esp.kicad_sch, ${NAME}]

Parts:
S6: ESP Reset; KMR_2; Mouser Part Number 611-KMR221G-LFS

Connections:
/ES_RST: S6.2, S6.4; also elsewhere on the board
GND: S6.1, S6.3; also elsewhere on the board

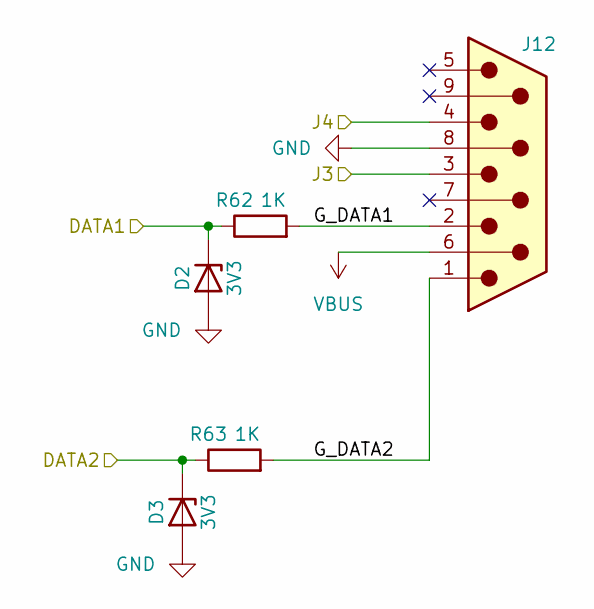
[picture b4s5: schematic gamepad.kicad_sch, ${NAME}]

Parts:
D2, D3: 3V3; D_SOD-323
J12: GP2; DSUB-9_Male_TopMount
R62, R63: 1K; R_0603_1608Metric

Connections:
/Gamepad/G_DATA1: J12.2, R62.2
/Gamepad/G_DATA2: J12.1, R63.2
/M20_ES_TX_GP: J12.4; also elsewhere on the board
/M21_ES_RX_GP: J12.3; also elsewhere on the board
/M26_GP_DATA1: D2.1 (K), R62.1; also elsewhere on the board
/M27_GP_DATA2: D3.1 (K), R63.1; also elsewhere on the board
GND: D2.2 (A), D3.2 (A), J12.8; also elsewhere on the board
VBUS: J12.6; also elsewhere on the board
